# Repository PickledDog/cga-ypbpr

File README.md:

# cga-ypbpr
 CGA/Tandy/EGA/Hercules to component video converter

Two units stacked, showing both sides

## Overview
Pre-VGA PCs use a handful of distinct video card types (CGA, Tandy, EGA, Hercules, MDA) to produce video. These have specific (but related) signaling systems, and all share a 9-pin D-Sub connector. This device converts these video signals into analog component video.

## Principle of operation
The above video systems use simple TTL digital signaling, which can be interpreted with gate logic (in this case, a GAL chip). Resistors are used to form a simple DAC for the analog outputs. This GAL has 10 outputs, providing 4 bits of precision for the Y (luminance) channel, and 3 bits each for Pb (blue) and Pr (red). This is the same basic concept as [Necroware's design](https://github.com/necroware/mce-adapter) and the [GGlabs CGA2RGB](https://gglabs.us/node/2284), just with YPbPr instead of RGBS output. Like these, it does format conversion but *not* scan conversion - the output signal has the same video timings as the input. A pulse stretching circuit adds a blank area to the beginning of each scanline, so that the TV (or scan converter) can set its black level, even if the PC is displaying a border. A simple lowpass filter provides detection of sync polarity, allowing the logic to autoswitch between CGA and other modes. Mono and EGA high-res modes can't be distinguished by polarity alone, so a switch is provided to select between them.

### Why component video?
It seems to be absent from the usual conversion options, with most converters of this type converting to 15.7kHz VGA (which is hard to accommodate since most monitors won't sync this) or SCART (which isn't common outside of Europe). Component, on the other hand, can be used directly with many TVs (CRT *and* LCD). It can also be run into scan converters, which commonly take this format. In addition, high quality cables are cheap and readily available for component video.

### So, about mono and high-res EGA...
This is where things get a little less "it just works". Unfortunately, neither of these produce video timings that are normal for component video. Tests with various component devices has yielded mixed results (although the [OSSC](https://videogameperfection.com/products/open-source-scan-converter/) is happy to work with this). 200-line modes worked in all cases, as expected (CGA uses standard NTSC video timings).

### I didn't understand any of that. What's this mean to me?
It means that you can connect any CGA, Tandy, or EGA source to any TV with a component video input. You can't use a VGA monitor (unless you add a scan converter). For EGA to work with all displays, you'll need to set the card to always use 200-line video modes. On most EGAs, this is done by setting the first 4 DIP switches to Off, Off, Off, On.

### Can I connect a Commodore 128?
Probably? I don't have a C128. These use the same signaling and pinout as CGA, so they should work.

## Power and cabling
Required power is 9V DC through a 2.1x5.5mm barrel jack, center positive. Any current/power rating should work - the device draws, at worst, 135mA (when using the non-ZeroPower version of the ATF22V10). With any luck, you already have a power brick with this voltage and connector. If you don't, you can [add one](https://www.mouser.com/ProductDetail/552-AA03A-090A-R) to your Mouser order. Component cables can be easily sourced, and 3 composite video cables are usable in a pinch. The required PC video cable is a male-to-male D-Sub DE-9 cable (all pins wired straight through). This can be [bought from Serdaco](https://www.serdashop.com/9-Pin-video-cable-2m) or built. To build one, you'll need two [DE-9 male plugs](https://www.mouser.com/ProductDetail/523-L717SDE09P), two [backshells](https://www.mouser.com/ProductDetail/156-2009-EX), and some shielded 9-core cable (connect the shield to pin 1). A modem cable can be used, but you'll probably need a gender changer as these are usually male-female. A *null* modem cable ***will not work*** as they have pins swapped.

## Assembly
The device is designed to fit in a common Hammond 1593K enclosure. The project provides 3 PCBs - the main board, and two that serve as the side panels. These should all be ordered at the standard 1.6mm thickness (if you have any colour preference for the side panels, remember to select it while ordering). With boards and components in hand, you can go ahead and solder everything down. Install the power LED "floating" above the board so it can be pushed into the hole in the panel, and mount the trimmer pot as high as its legs will allow to make adjustment easier. Once all components have been soldered into the main board, slide the side panels on over the jacks and switches, and lower the whole assembly into the lower case half, with the panels aligned to the case grooves. Don't install the chip in the socket yet though - we need to program it first.

### Programming the GAL
The ATF22V10 can be programmed in an EPROM programmer, like a TL866 [or T48](https://xgecu.myshopify.com/collections/xgecu-t48-tl866ii-3g-programmer). Source and compiled output are in the `pld` folder. Programming the chip just needs the `cga-ypbpr.jed` file.

### (optional) Editing the GAL source
The source `cga-ypbpr.pld` can be edited in WinCUPL, which is downloaded for free [from Microchip](https://www.microchip.com/en-us/products/fpgas-and-plds/spld-cplds/pld-design-resources). The following compiler options (under Options → Compiler) are required to build it:

- Minimization: Select **Quine-McCluskey**
- Optimization: Check **Best For Polarity**, uncheck all others

### Adjusting the trimmer potentiometer
The trimmer adjusts how long the blanking period applied to the beginning of each scanline is. This blanking is only applied in 200-line modes (the fat "CGA border" is unique to these modes); for EGA cards, see the note above about EGA DIP switches. Start by turning the trimmer all the way to the minimum position (counter-clockwise), then power the unit (and suitable old computer) on. Next, load up a game that uses a border (Keen 4 works well), or enter `COLOR , , 5` in GW-Basic/QBasic. The screen should visibly dim (and turn the wrong colour), due to the video decoder in the TV or scan converter "seeing" the border where there should be black. Now turn the trimmer clockwise and the screen will get brighter - stop turning when it no longer has an effect on brightness. You can turn it further, but a black bar will appear on the left hand side and start covering part of the screen. Many EGA cards insert their own blanking, and don't dim even in the leftmost position (very nice!); for these, set the trimmer so the black bar is just offscreen.

## Parts list
Bill Of Materials and part references are below. The specified parts are just the ones I used, and can be substituted as needed - Mouser links provided for convenience and reference. The case is available in other colours!

| Reference | Value | Qty | Mouser link |
| --------- | ----- | --- | ----------- |
| C1-C3 | 1μF ceramic | 3 | [KEMET C315C105K3R5TA](https://www.mouser.com/ProductDetail/80-C315C105K3R) |
| C4 | 100μF electrolytic | 1 | [Panasonic ECA-1VM101I](https://www.mouser.com/ProductDetail/667-ECA-1VM101I) |
| C5-C7 | 47pF ceramic | 3 | [KEMET C315C470K2G5TA](https://www.mouser.com/ProductDetail/80-C315C470K2G) |
| C8 | 1nF ceramic | 1 | [KEMET C315C102K1R5TA](https://www.mouser.com/ProductDetail/80-C315C102K1R) |
| D1 | 3mm green LED | 1 | [Lite-On LTL-4231N](https://www.mouser.com/ProductDetail/859-LTL-4231N) |
| FB1 | Ferrite bead | 1 | [Wurth 7427502](https://www.mouser.com/ProductDetail/710-7427502) |
| J1 | D-Sub DE-9 female | 1 | [Amphenol L77SDE09SA4CH4F](https://www.mouser.com/ProductDetail/523-L77SDE09SA4CH4F) |
| J2 | 2.1x5.5mm barrel | 1 | [CUI PJ-002A](https://www.mouser.com/ProductDetail/490-PJ-002A) |
| J3 | RCA, green | 1 | [Kycon KLPX-0848A-2-GR](https://www.mouser.com/ProductDetail/806-KLPX-0848A-2-GR) |
| J4 | RCA, blue | 1 | [Kycon KLPX-0848A-2-BL](https://www.mouser.com/ProductDetail/806-KLPX-0848A-2-BL) |
| J5 | RCA, red | 1 | [Kycon KLPX-0848A-2-R](https://www.mouser.com/ProductDetail/806-KLPX-0848A-2-R) |
| Q1, Q2 | 2N7000 | 2 | [onsemi 2N7000](https://www.mouser.com/ProductDetail/512-2N7000BU) |
| R1, R6, R10 | 732Ω 1% | 3 | [YAGEO MFR-25FRF52-732R](https://www.mouser.com/ProductDetail/603-MFR-25FRF52-732R) |
| R2, R7, R11 | 1k43Ω 1% | 3 | [YAGEO MFR-25FRF52-1K43](https://www.mouser.com/ProductDetail/603-MFR-25FRF521K43) |
| R3, R8, R12 | 2k87Ω 1% | 3 | [YAGEO MFR-25FRF52-2K87](https://www.mouser.com/ProductDetail/603-MFR-25FRF522K87) |
| R4, R9, R13 | 150Ω 1% | 3 | [YAGEO MFR-25FTF52-150R](https://www.mouser.com/ProductDetail/603-MFR-25FTF52-150R) |
| R5 | 365Ω 1% | 1 | [YAGEO MFR-25FRF52-365R](https://www.mouser.com/ProductDetail/603-MFR-25FRF52-365R) |
| R14, R17 | 10kΩ 5%| 2 | [YAGEO CFR-25JB-52-10K](https://www.mouser.com/ProductDetail/603-CFR-25JB-52-10K) |
| R15 | 330Ω 5% | 1 | [YAGEO CFR-25JB-52-330R](https://www.mouser.com/ProductDetail/603-CFR-25JB-52-330R) |
| R16 | 1kΩ 5% | 1 | [YAGEO CFR-25JR-52-1K](https://www.mouser.com/ProductDetail/603-CFR-25JR-521K) |
| RV1 | 10k linear | 1 | [Piher PT10LH01-103A](https://www.mouser.com/ProductDetail/531-PT10H-10K) |
| SW1 | SPDT toggle | 1 | [Grayhill 34CMSP12B2M7QT](https://www.mouser.com/ProductDetail/706-34CMSP12B2M7QT) |
| SW2 | SPDT slide | 1 | [C&K OS102011MA1QN1](https://www.mouser.com/ProductDetail/611-OS102011MA1QN1) |
| U1 | MCP1702-500 | 1 | [Microchip MCP1702-5002E](https://www.mouser.com/ProductDetail/579-MCP1702-5002E/TO) |
| U2 | ATF22V10C | 1 | [Atmel ATF22LV10CQZ-30](https://www.mouser.com/ProductDetail/556-AF22LV10CQZ-30PU) |
| | socket | 1 | [Amphenol DILB24P-224TLF](https://www.mouser.com/ProductDetail/649-DILB24P-224TLF) |
| Case | Hammond 1593K | 1 | [Hammond 1593KTBU](https://www.mouser.com/ProductDetail/546-1593KTBU) |
| Screws | Hammond self-tapping | (4 of) | [Hammond 1593ATS](https://www.mouser.com/ProductDetail/546-1593ATS100) |

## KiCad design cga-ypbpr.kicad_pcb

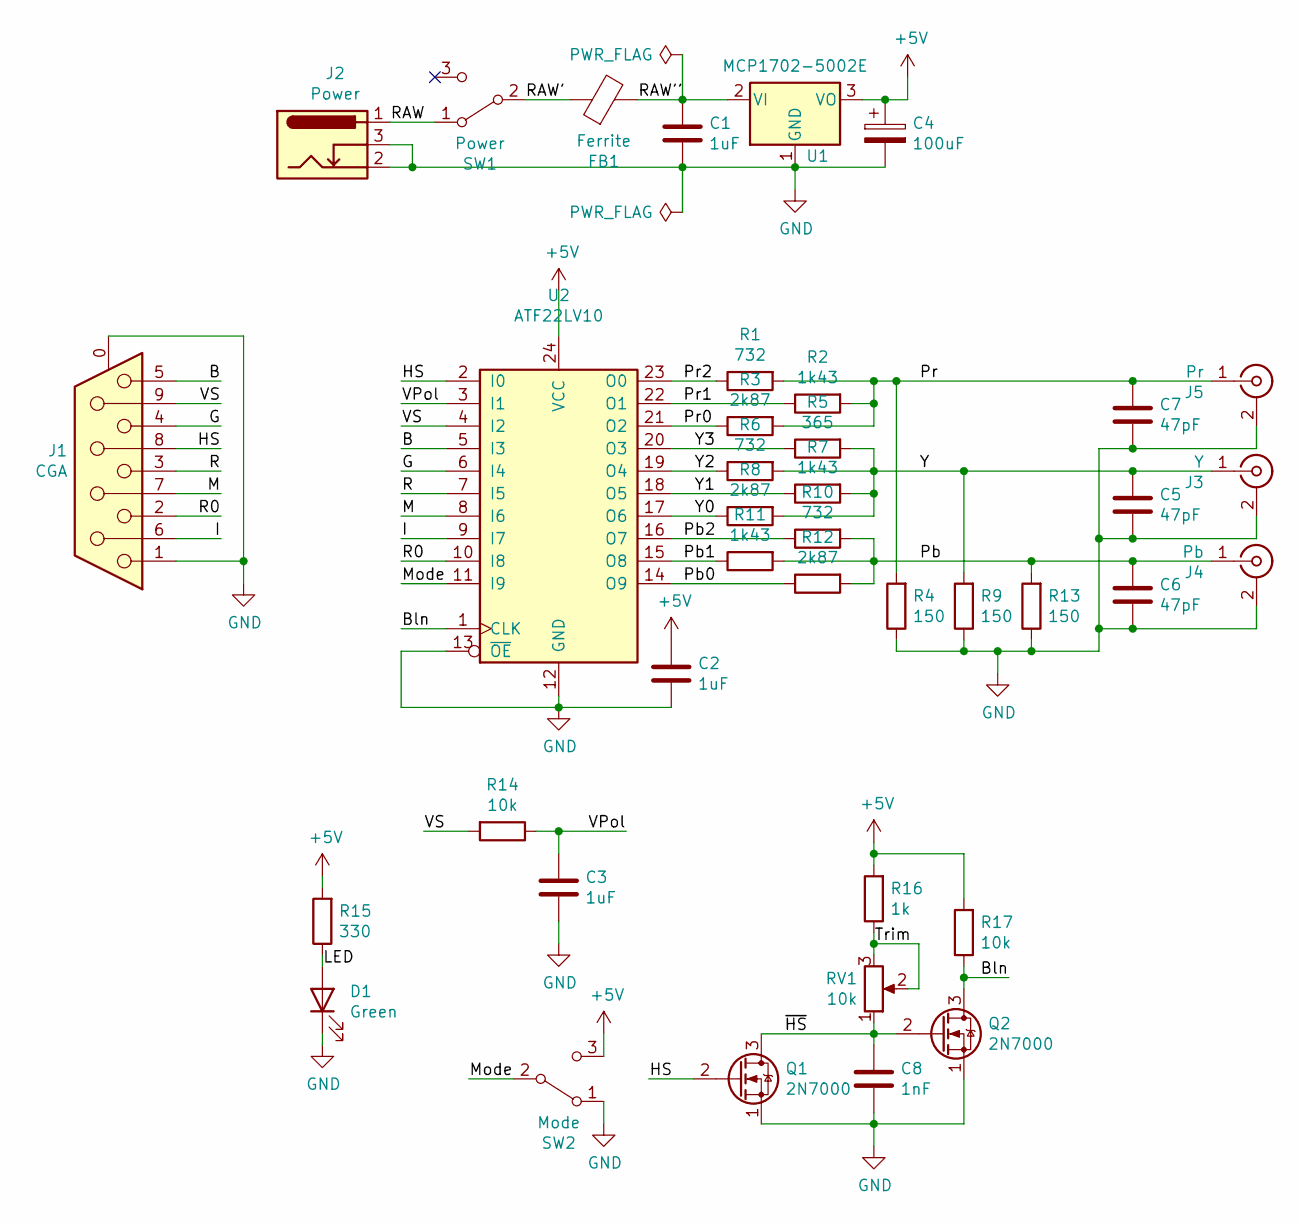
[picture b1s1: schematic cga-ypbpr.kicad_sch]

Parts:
C1, C2, C3: 1uF; C_Disc_D3.0mm_W2.0mm_P2.50mm
C4: 100uF; CP_Radial_D6.3mm_P2.50mm
C5, C6, C7: 47pF; C_Disc_D3.0mm_W1.6mm_P2.50mm
C8: 1nF; C_Disc_D3.0mm_W1.6mm_P2.50mm
D1: Green; LED_D3.0mm
FB1: Ferrite; L_Axial_L9.5mm_D4.0mm_P12.70mm_Horizontal_Fastron_SMCC
J1: CGA; DSUB-9_Female_Horizontal_P2.77x2.84mm_EdgePinOffset7.70mm_H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
J2: Power; BarrelJack_Horizontal
J3: Y; RCA_Unswitched
J4: Pb; RCA_Unswitched
J5: Pr; RCA_Unswitched
Q1, Q2: 2N7000; TO-92
R1, R6, R10: 732; R_Axial_DIN0207_L6.3mm_D2.5mm_P7.62mm_Horizontal
R2, R7, R11: 1k43; R_Axial_DIN0207_L6.3mm_D2.5mm_P7.62mm_Horizontal
R3, R8, R12: 2k87; R_Axial_DIN0207_L6.3mm_D2.5mm_P7.62mm_Horizontal
R4, R9, R13: 150; R_Axial_DIN0207_L6.3mm_D2.5mm_P7.62mm_Horizontal
R5: 365; R_Axial_DIN0207_L6.3mm_D2.5mm_P7.62mm_Horizontal
R14, R17: 10k; R_Axial_DIN0207_L6.3mm_D2.5mm_P7.62mm_Horizontal
R15: 330; R_Axial_DIN0207_L6.3mm_D2.5mm_P7.62mm_Horizontal
R16: 1k; R_Axial_DIN0207_L6.3mm_D2.5mm_P7.62mm_Horizontal
RV1: 10k; Potentiometer_Piher_PT-10-H01_Horizontal
SW1: Power; SW_Toggle_SPDT_Vertical
SW2: Mode; SW_CuK_OS102011MA1QN1_SPDT_Angled
U1: MCP1702-5002E; TO-92
U2: ATF22LV10; DIP-24_W7.62mm_Socket_LongPads

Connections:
+5V: C2.1, C4.1, R15.2, R16.2, R17.2, SW2.3 (C), U1.3 (VO), U2.24 (VCC)
/B: J1.5, U2.5 (I3)
/Bln: Q2.3 (D), R17.1, U2.1 (CLK)
/G: J1.4, U2.6 (I4)
/HS: J1.8, Q1.2 (G), U2.2 (I0)
/I: J1.6, U2.9 (I7)
/LED: D1.2 (A), R15.1
/M: J1.7, U2.8 (I6)
/Mode: SW2.2 (B), U2.11 (I9)
/Pb: C6.1, J4.1 (In), R10.2, R11.2, R12.2, R13.2
/Pb0: R12.1, U2.14 (O9)
/Pb1: R11.1, U2.15 (O8)
/Pb2: R10.1, U2.16 (O7)
/Pr: C7.1, J5.1 (In), R1.2, R2.2, R3.2, R4.2
/Pr0: R3.1, U2.21 (O2)
/Pr1: R2.1, U2.22 (O1)
/Pr2: R1.1, U2.23 (O0)
/R: J1.3, U2.7 (I5)
/R0: J1.2, U2.10 (I8)
/RAW: J2.1, SW1.1 (A)
/RAW': FB1.1, SW1.2 (B)
/RAW'': C1.1, FB1.2, U1.2 (VI)
/Trim: R16.1, RV1.2, RV1.3
/VPol: C3.1, R14.1, U2.3 (I1)
/VS: J1.9, R14.2, U2.4 (I2)
/Y: C5.1, J3.1 (In), R5.2, R6.2, R7.2, R8.2, R9.2
/Y0: R8.1, U2.17 (O6)
/Y1: R7.1, U2.18 (O5)
/Y2: R6.1, U2.19 (O4)
/Y3: R5.1, U2.20 (O3)
/~HS: C8.1, Q1.3 (D), Q2.2 (G), RV1.1
GND: C1.2, C2.2, C3.2, C4.2, C5.2, C6.2, C7.2, C8.2, D1.1 (K), J1.0 (PAD), J1.1, J2.2, J2.3, J3.2 (Ext), J4.2 (Ext), J5.2 (Ext), Q1.1 (S), Q2.1 (S), R4.1, R9.1, R13.1, SW2.1 (A), U1.1 (GND), U2.12 (GND), U2.13 (~OE)

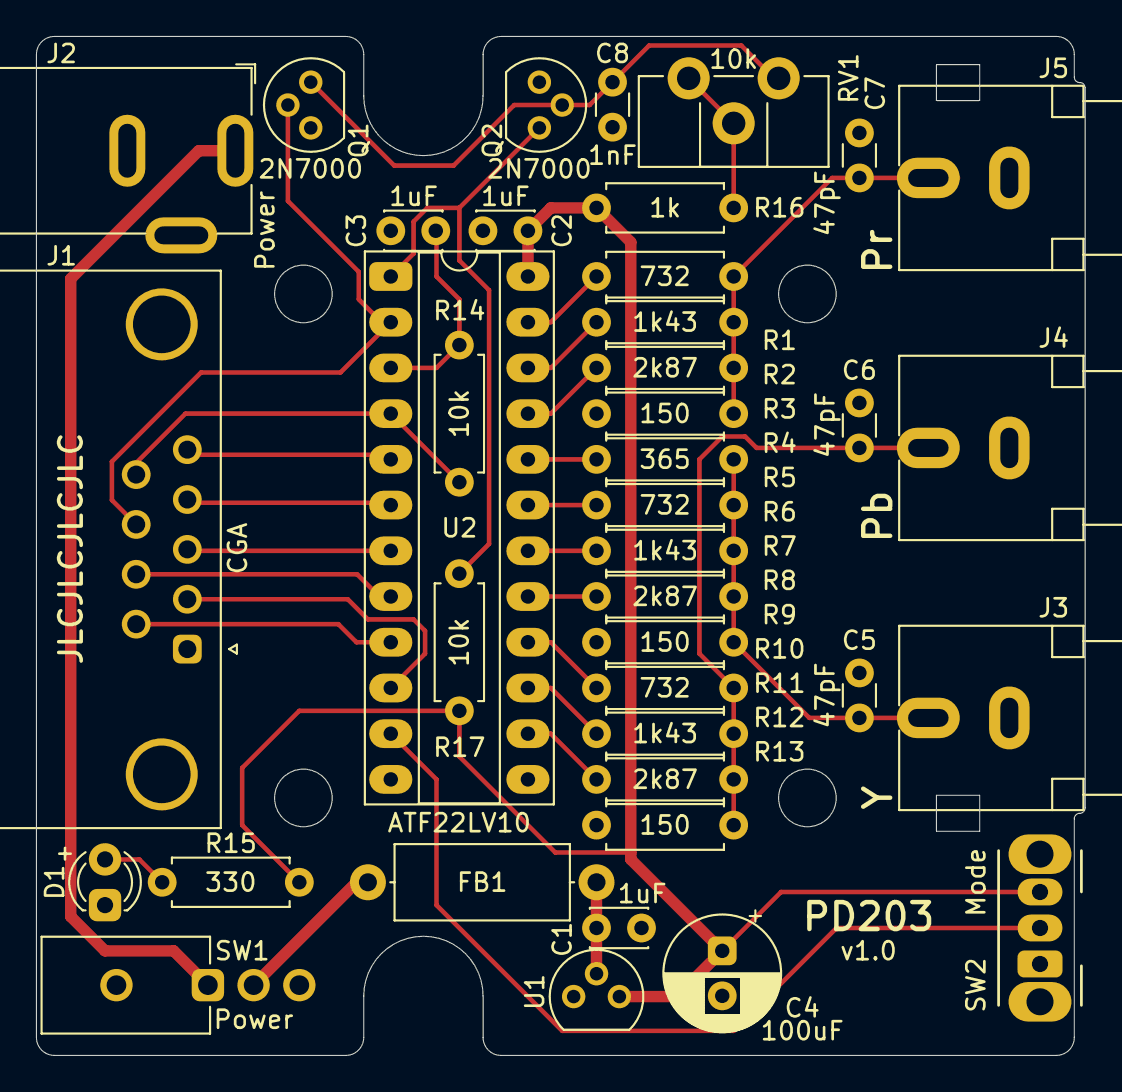
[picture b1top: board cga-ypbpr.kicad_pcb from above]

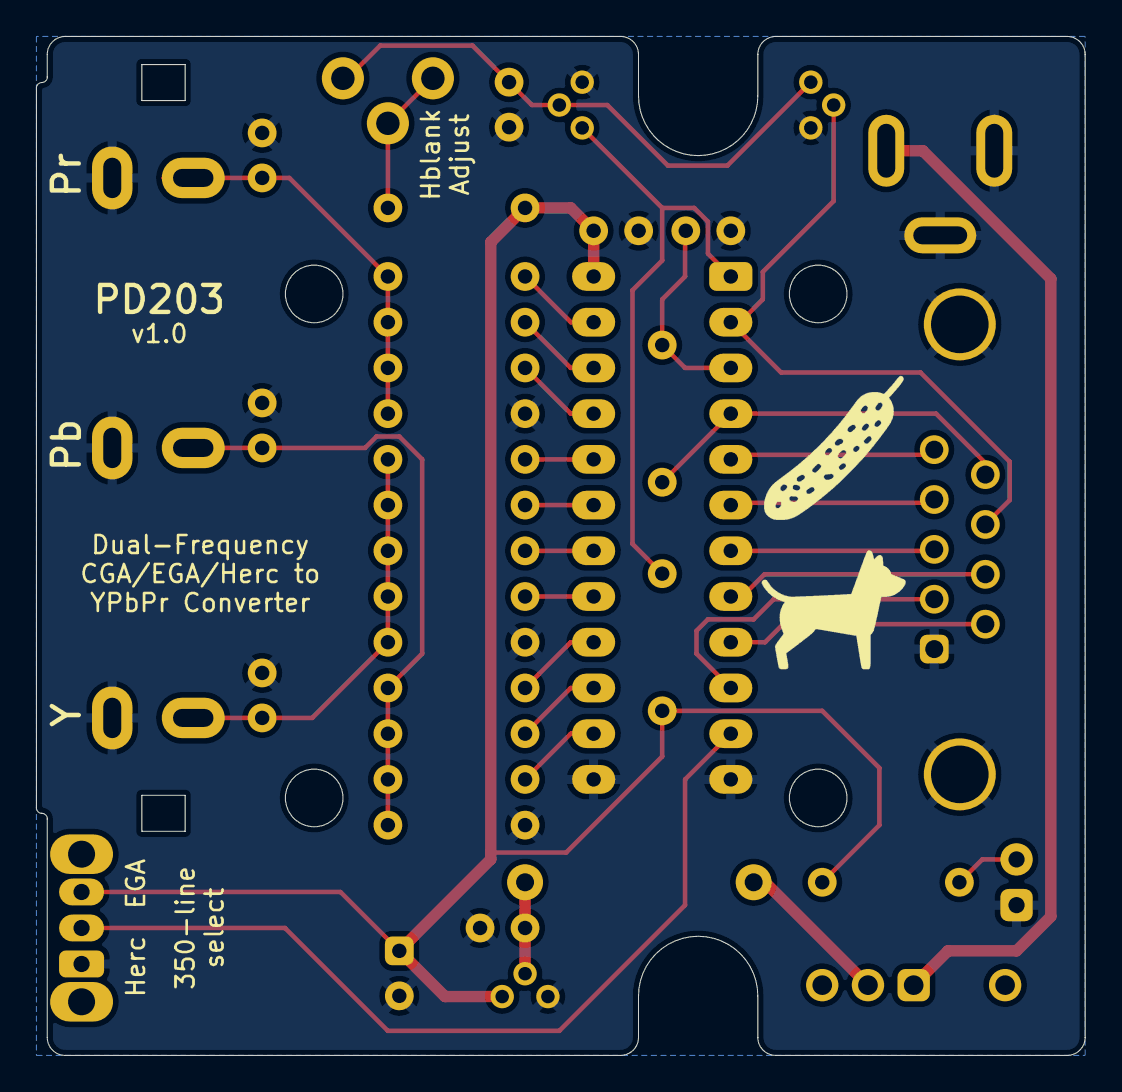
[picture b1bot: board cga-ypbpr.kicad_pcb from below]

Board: 2 copper layers, 58.3 x 56.6 mm, 45 parts (2 on the bottom side), 32 nets.

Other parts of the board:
MK1, MK2, MK3, MK4: Mounting_Hole; MountingHole_3.2mm_M3_ISO7380
Ref**: Val**; Symbol-Pickle-8mm
Ref**#2: Val**; Symbol-Dog-8mm

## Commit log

2023-07-16 Add README and product pics
2023-07-26 Serdaco sells the necessary cable - noted!
